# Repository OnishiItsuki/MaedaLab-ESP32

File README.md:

# Library for ESP32

2022/02/15 \
Itsuki Onishi \
E-mail : onishi.itsuki@ist.osaka-u.ac.jp

このレポジトリはESP32，ArduinoIDE環境で書かれたプログラム群です．

ESP32をArduino IDEで使うためにボード情報をインストールします． \
詳細は下記のサイトを参照してください．
 * https://github.com/espressif/arduino-esp32
 * https://dandydot.no-ip.biz/~dot/presen/advtech/seminars/iot_workshop/install-esp32-board-manager/README.md.html .

レバー角読み取りのコードは`lever_angle_reader`，モータ制御コードは`PWM_motor_controller`にあります．
それぞれの詳細は各ディレクトリ下のREADMEを読んでください．

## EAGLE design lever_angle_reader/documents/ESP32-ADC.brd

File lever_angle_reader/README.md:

# Lever angle reader for ESP32

2022/02/15 \
大西 幾月 \
E-mail : onishi.itsuki@ist.osaka-u.ac.jp

## 機能
このプログラムは，AD converter（以降ADCと記載）によるレバー角の測定と結果の送信を行います． \
操作対象となるデバイスは下記の通りです．
括弧内に使用したデバイスの型番を記載します．
  * ADC (LTC2309)
  * OLED display (SSD1306)
  * Signal LED

プログラムの流れは下記のとおりです．
  1. ESP32，ADC，OLED display，LEDの初期化．
  2. ADCに読み取りのための信号をI2Cを用いて送信．
  3. ADCから測定された電圧を受信．
  4. 電圧からPWM制御信号を生成．
  5. 測定結果をPWM_motor_controllerを稼働させているESP32に送信．
  6. 2から5の処理を繰り返す．

このプログラムは"PWM_motor_controller"とセットで使います．
"PWM_motor_controller"の詳細は同名のディレクトリ下にあるREADMEを参照してください．

## 依存環境
ESP32をArduino IDEで使うためにボード情報をインストールします． \
詳細は下記のサイトを参照してください．
 * https://github.com/espressif/arduino-esp32
 * https://dandydot.no-ip.biz/~dot/presen/advtech/seminars/iot_workshop/install-esp32-board-manager/README.md.html .

依存するライブラリを列挙します．
それぞれのライブラリの詳細はライブラリ名の下に記載したサイトを参照してください．

  * ESP8266 and ESP32 driver for SSD1366 displays
    * https://wak-tech.com/archives/825
    * https://github.com/ThingPulse/esp8266-oled-ssd1306

## ファイル構成
このプログラムのファイル構成は下記の通りです．
```  
.  
|-- documents
|   |-- ESP32-ADC.brd           # このデバイスの基盤設計図（ボード情報）
|   |-- ESP32-ADC.sch           # このデバイスの基盤設計図（配線情報）
|   --- LTC2309.pdf             # ADC (LTC2309)のデータシート
|
|-- lever_angle_reader.ino      # Main
|-- ADC_controller.ino          # ADC用の関数と変数
|-- OLED_controller.ino         # OLED用の関数と変数
|-- SIGNAL_LED_controller.ino   # Signal LED用の関数
|-- UDP_Tx.ino                  # WiFi+UDPによる信号送信用の関数
--- README.md                   # このファイル
```

## 通信フォーマット
"PWM_motor_controller"下のREADME内の同項目を参照してください．

## 関数リスト
各ファイルにある関数の情報です．
各ファイル内でのみアクセスする関数は"_"を先頭に付けています．

### lever_angle_reader.ino
| 関数名 | 構文 | 機能 | 返り値 | 処理説明 | 備考 |
| :---: | :---: | :---: | :---: | :---: | :---: |
| setup | setup() | デバイス全体の初期化 | Nan | ESP32，AD converter，OLED，LEDの初期化とチェック処理 |  |
| loop | loop() | ESP32のmain loop | Nan | レバー角の読み取りと送信 |  |

### ADC_controller.ino
| 関数名 | 構文 | 機能 | 返り値 | 処理説明 | 備考 |
| :---: | :---: | :---: | :---: | :---: | :---: |
| ADC_init | ADC_init() | ADCの利用時に`setup()`で呼ぶ関数 | Nan | ADCのデバイスの初期化（？）とESP32側でのADC利用のための処理 | 未実装 |
| _send_read_signal | _send_read_signal() | ADCに読み取り信号を送る． | Nan | ADC用にI2C回線を専有し，読み取り信号を送信する．step2の処理に相当する． | 未実装 |
| _receive_voltage_values | _receive_voltage_values(int buffer[]) | ADCから観測値を取得する． | Nan | ADCから観測値を取得し，受け取った配列に格納する．step3の処理に相当する．| 未実装 |
| read_voltage_from_ADC | read_voltage_from_ADC(int buffer[]) | ADCから観測値を取得する． | Nan | `lever_angle_reader.ino`からADCにアクセスするための関数．内部では_send_read_signalと_receive_voltage_valuesを呼び出している． |  |

### OLED_controller.ino
| 関数名 | 構文 | 機能 | 返り値 | 処理説明 | 備考 |
| :---: | :---: | :---: | :---: | :---: | :---: |
| OLED_init | OLED_init() | OLEDディスプレイの利用時に`setup()`で呼ぶ関数 | Nan | ディスプレイの初期化と異常検知用の全要素表示を行う． |  |
| disp_init | disp_init() | ディスプレイの初期化 | Nan | 初期化とフォント（フォントサイズを含む）設定を行う． |  |
| OLED_clear | OLED_clear() | ディスプレイの表示を消す | Nan | ディスプレイの表示を消す． | 今はdisp_init()を呼び出すことで実装している．もう少しいい方法があるかも． |
| disp_all_pixel | disp_all_pixel() | 全画素をONにする | Nan | 全画素をONにする |  |
| disp_add_string | disp_add_string(int16_t x, int16_t y, String message) | ディスプレイに文字を表示する． | Nan | messageに入力された文字列を(x, y)の位置に出力する．過去のディスプレイの表示は消されずに追加される． |  |
| disp_show_string | disp_show_string(String message) | 入力された文字列を成型して表示 | Nan | messageで入力された文字列を画面端もしくは"\n"で折り返す．縦方向には特に処理を行わないのであまり多くの文字を各と画面下で文字が切れる．（簡単な判定で警告を出す機能はある．） | 2行まではうまく表示できるはず．．．あまり期待した動作をしなさそうです．．． |

### SIGNAL_LED_controller.ino
| 関数名 | 構文 | 機能 | 返り値 | 処理説明 | 備考 |
| :---: | :---: | :---: | :---: | :---: | :---: |
| LED_init | LED_init() | LEDを使うときに最初に呼び出す関数 | Nan | ピンアサインを行う．PIN番号はSIGNAL_LED_PINにより設定する． |  |
| led_on | led_on() | LEDを点灯する． | Nan | LEDを点灯する． |  |
| led_off | led_off() | LEDを消灯する． | Nan | LEDを消灯する． |  |

### UDP_Tx.ino
| 関数名 | 構文 | 機能 | 返り値 | 処理説明 | 備考 |
| :---: | :---: | :---: | :---: | :---: | :---: |
| _WiFi_setup | _WiFi_setup(String message) | ESP32間の通信を担うWiFiの初期化 | Nan | WiFiインスタンスの初期化と設定を行う．Serial通信とディスプレイでの状態表示をも行う．messageには何のために呼び出されたかの説明を入れる． | WiFiが接続されるまでloopし続けるので注意．（特に単体でdebugするとき） |
| _signal_buffer_init | _signal_buffer_init() | signal_bufferの初期化 | Nan | signal_bufferを初期化する． |  |
| UDP_init | UDP_init() | ESP32間の通信を行う際に`setup()`で呼ぶ関数 | Nan | UDPを用いたWiFiの初期化処理と接続を行う．接続に成功したらその旨をSerial通信とディスプレイで表示する． |  |
| _compute_signal_from_voltage | _compute_signal_from_voltage(int voltage_value) | WiFiで送信される値を計算する |WiFiで送信される値 | ADCで観測した電圧からWiFiで送信する値を計算する．入力，出力ともに配列ではなく，値であることに注意． | 現状intからuint8_tにコンバートするだけの関数になっている． |
| _compute_parity | _compute_parity(uint8_t signal_buffer[]) | parity bitの値を計算する | parity bitの値 | index 1からindex NUM_CH-2までにWiFiで送信される値を格納した配列を受け取り，parity bitの値を計算して返す． |  |
| _generate_udp_signal_from_voltage | _generate_udp_signal_from_voltage(int voltage[]) | WiFiで送信する値の生成 | Nan | ADCで観測した値の配列からWiFiで送信する信号を生成する．結果はsignal_bufferに格納される． |  |
| _send_signal | _send_signal() | WiFiでsignal_bufferの値を送信する | Nan | WiFiの接続を確認し，signal_bufferの値を送信する．WiFiの接続が切れていた場合は再接続処理を行う．急激な動きを防ぐために，関数の実行後に送信の可否に寄らずsignal_bufferの値は初期化される． | WiFiが接続されない間はloopし続けるので注意 |
| send_udp_signal | send_udp_signal(int voltage[]) | ADCの観測結果をWiFiで送信する | Nan | ADCでの観測結果を受け取り，前処理の後にWiFiで相手のESP32に送信する． |  |

## 変数リスト
各ファイルにある変数の情報です．
local変数については説明を省略します．
マクロは大文字スネーク記法，変数は小文字スネーク記法（省略した単語は大文字）で書いています．
設定値は基本的にマクロで書いています．

### lever_angle_reader.ino
| 変数名 | 用途 | 備考 |
| :---: | :---: | :---: |
| SDA_PIN | I2C通信のSDAのPINを決める．使えるPINに制約があるので，ググって調べてください． | デフォルトは21（`ADC_controller.ino`と`OLED_controller.ino`で定義） |
| SCL_PIN | I2C通信のSCLのPINを決める．使えるPINに制約があるので，ググって調べてください． | デフォルトは22（`ADC_controller.ino`と`OLED_controller.ino`で定義） |
| SIGNAL_LED_PIN | LEDの制御PINを決める． | デフォルトは27（`SIGNAL_LED_controller.ino`で定義） |
| NUM_CH | ADCで読み取る信号のチャネル数．6で固定でOK（マジックナンバー回避が目的のため） |  |
| voltage_buffer | ADCで読み取った数値を格納する配列． | 現在はint型にしていますが，ADCの仕様に合わせて変えてください． |

### ADC_controller.ino
| 変数名 | 用途 | 備考 |
| :---: | :---: | :---: |
| SDA_PIN | I2C通信のSDAのPINを決める．使えるPINに制約があるので，ググって調べてください． | この値は基本的に変更しない．一時的に変更する場合は，`lever_angle_reader.ino`に書く． |
| SCL_PIN | I2C通信のSCLのPINを決める．使えるPINに制約があるので，ググって調べてください． | この値は基本的に変更しない．一時的に変更する場合は，`lever_angle_reader.ino`に書く． |
| MAX_SLAVE_RESPONSE_LENGTH | ADCに要求するバイト数． | ADC実装後に確認 |
| ADC_ADDR | ADCのI2C通信におけるアドレス． |  |

### OLED_controller.ino
| 変数名 | 用途 | 備考 |
| :---: | :---: | :---: |
| SDA_PIN | I2C通信のSDAのPINを決める．使えるPINに制約があるので，ググって調べてください． | この値は基本的に変更しない．一時的に変更する場合は，`lever_angle_reader.ino`に書く． |
| SCL_PIN | I2C通信のSCLのPINを決める．使えるPINに制約があるので，ググって調べてください． | この値は基本的に変更しない．一時的に変更する場合は，`lever_angle_reader.ino`に書く． |
| OLED_ADDR | OLEDディスプレイのI2C通信でのアドレス． |  |
| FONT | ディスプレイのフォントとフォントサイズを決める．入力値の詳細はググってください． |  |
| font_size_width | フォントの横幅に相当する定数．これでフォントサイズが変わるわけでは無く，`disp_show_string`の成型に影響する．表示を見ながら適当に設定指定ください． |  |
| font_size_height | フォントの縦幅に相当する定数．これでフォントサイズが変わるわけでは無く，`disp_show_string`の成型に影響する．表示を見ながら適当に設定指定ください． |  |
| disp_width | ディスプレイの横幅．`disp_all_pixel`などで使用している． | 調整済みなので，128から変更しない．
| disp_height | ディスプレイの縦幅．`disp_all_pixel`などで使用している． | 調整済みなので，64から変更しない． |
| max_num_char_width | 横幅に入る最大文字数．上記の変数から計算するので設定不要． |  |
| max_num_line | ディスプレイに表示できる最大行数．上記の変数から計算するので設定不要． |  |

### SIGNAL_LED_controller.ino
| 変数名 | 用途 | 備考 |
| :---: | :---: | :---: |
| SIGNAL_LED_PIN | LEDの制御PINを決める． | この値は基本的に変更しない．一時的に変更する場合は，`lever_angle_reader.ino`に書く． |

### UDP_Tx.ino
| 変数名 | 用途 | 備考 |
| :---: | :---: | :---: |
| SSID | WiFiホストのSSID．なんでもいいが，ホストと一致させる必要がある． |  |
| PASSWORD | WiFiホストのPASSWORD．なんでもいいが，ホストと一致指せる必要がある． |  |
| HOST_IP | WiFiホストのIP．なんでもいいが，ホストと一致指せる必要がある． |  |
| HOST_PORT | ホストのソケットのポート設定．なんでもいいが，ホストと一致指せる必要がある． |  |
| CLIENT_PORT | クライアントのソケットのポート設定．なんでもいい． |  |
| RECONNECTION_SPAN_MS | WiFiの接続が切れている時に接続を再確認する時間間隔． |  |
| signal_size | UDPで送信する信号のサイズ．スタートビット，各チャネルの信号，パリティビットで構成されるため，NUM_CH + 2となっている． |  |
| start_BYTE | スタートバイトの値． |  |
| signal_buffer | 送信する信号のbuffer． |  |

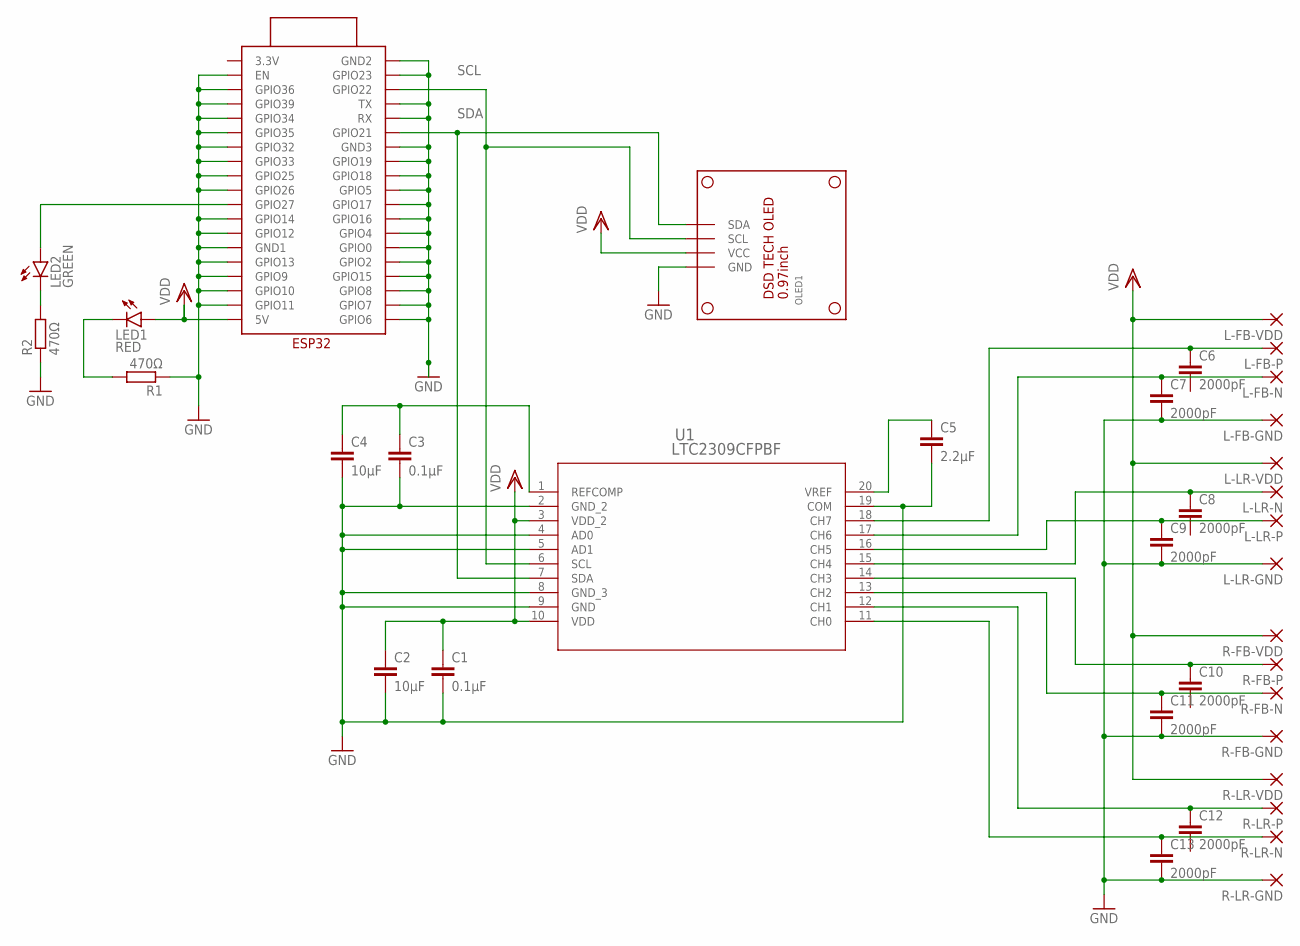
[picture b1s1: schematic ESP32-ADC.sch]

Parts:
C1, C3: 0.1µF; C3216
C2, C4: 10µF; C3216
C5: 2.2µF; C3216
C6, C7, C8, C9, C10, C11, C12, C13: 2000pF; C3216
L-FB-GND: SMD2; SMD1,27-2,54
L-FB-N: SMD2; SMD1,27-2,54
L-FB-P: SMD2; SMD1,27-2,54
L-FB-VDD: SMD2; SMD1,27-2,54
L-LR-GND: SMD2; SMD1,27-2,54
L-LR-N: SMD2; SMD1,27-2,54
L-LR-P: SMD2; SMD1,27-2,54
L-LR-VDD: SMD2; SMD1,27-2,54
LED1: RED; LED3MM
LED2: GREEN; LED3MM
OLED1: DSDTECH_ARDUINO_AVRCOMPATIBLE_IIC_OLED; DSDTECH0.96"ARDUINOAVRCOMPATIBLEIICOLEDLCDSCREENSUPPORTU8GL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
R1, R2: 470Ω; R3216W
R-FB-GND: SMD2; SMD1,27-2,54
R-FB-N: SMD2; SMD1,27-2,54
R-FB-P: SMD2; SMD1,27-2,54
R-FB-VDD: SMD2; SMD1,27-2,54
R-LR-GND: SMD2; SMD1,27-2,54
R-LR-N: SMD2; SMD1,27-2,54
R-LR-P: SMD2; SMD1,27-2,54
R-LR-VDD: SMD2; SMD1,27-2,54
U1: LTC2309CFPBF; TSSOP-20_F_LIT
U$2: ESP32ESP32_WIFI; ESP32_WIFI

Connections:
GND: C1.2, C2.2, C3.2, C4.2, C5.2, C7.2, C9.2, C11.2, C13.2, L-FB-GND.1, L-LR-GND.1, OLED1.GND, R1.1, R2.1, R-FB-GND.1, R-LR-GND.1, U1.2 (GND_2), U1.4 (AD0), U1.5 (AD1), U1.8 (GND_3), U1.9 (GND), U1.19 (COM), U$2.EN, U$2.GND1, U$2.GND2, U$2.GND3, U$2.GPIO0, U$2.GPIO2, U$2.GPIO4, U$2.GPIO5, U$2.GPIO6, U$2.GPIO7, U$2.GPIO8, U$2.GPIO9, U$2.GPIO10, U$2.GPIO11, U$2.GPIO12, U$2.GPIO13, U$2.GPIO14, U$2.GPIO15, U$2.GPIO16, U$2.GPIO17, U$2.GPIO18, U$2.GPIO19, U$2.GPIO23, U$2.GPIO25, U$2.GPIO26, U$2.GPIO32, U$2.GPIO33, U$2.GPIO34, U$2.GPIO35, U$2.GPIO36, U$2.GPIO39, U$2.RX, U$2.TX
unnamed: C5.1, U1.20 (VREF)
unnamed: LED2.A, U$2.GPIO27
unnamed: C6.1, L-FB-P.1, U1.18 (CH7)
unnamed: C7.1, L-FB-N.1, U1.17 (CH6)
unnamed: C9.1, L-LR-P.1, U1.16 (CH5)
unnamed: C8.1, L-LR-N.1, U1.15 (CH4)
unnamed: C10.1, R-FB-P.1, U1.14 (CH3)
unnamed: C11.1, R-FB-N.1, U1.13 (CH2)
unnamed: C13.1, R-LR-N.1, U1.11 (CH0)
unnamed: C12.1, R-LR-P.1, U1.12 (CH1)
unnamed: LED1.K (C), R1.2
unnamed: LED2.K (C), R2.2
SCL: OLED1.SCL, U1.6 (SCL), U$2.GPIO22
SDA: OLED1.SDA, U1.7 (SDA), U$2.GPIO21
VCC1: C3.1, C4.1, U1.1 (REFCOMP)
VDD: C1.1, C2.1, L-FB-VDD.1, L-LR-VDD.1, LED1.A, OLED1.VCC, R-FB-VDD.1, R-LR-VDD.1, U1.3 (VDD_2), U1.10 (VDD), U$2.5V

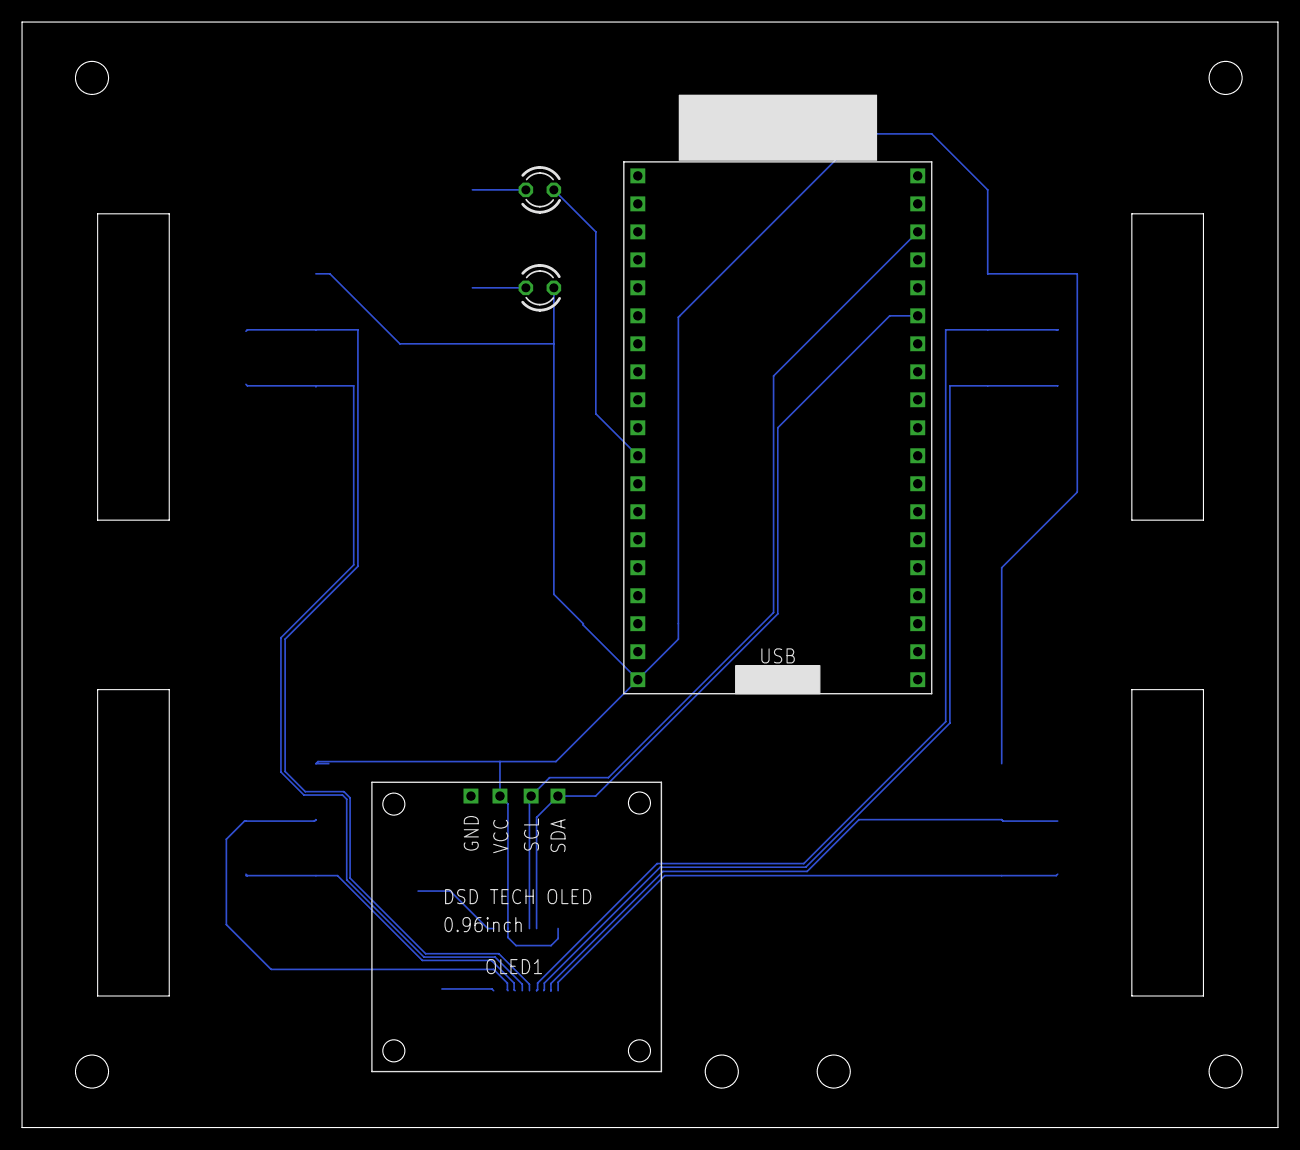
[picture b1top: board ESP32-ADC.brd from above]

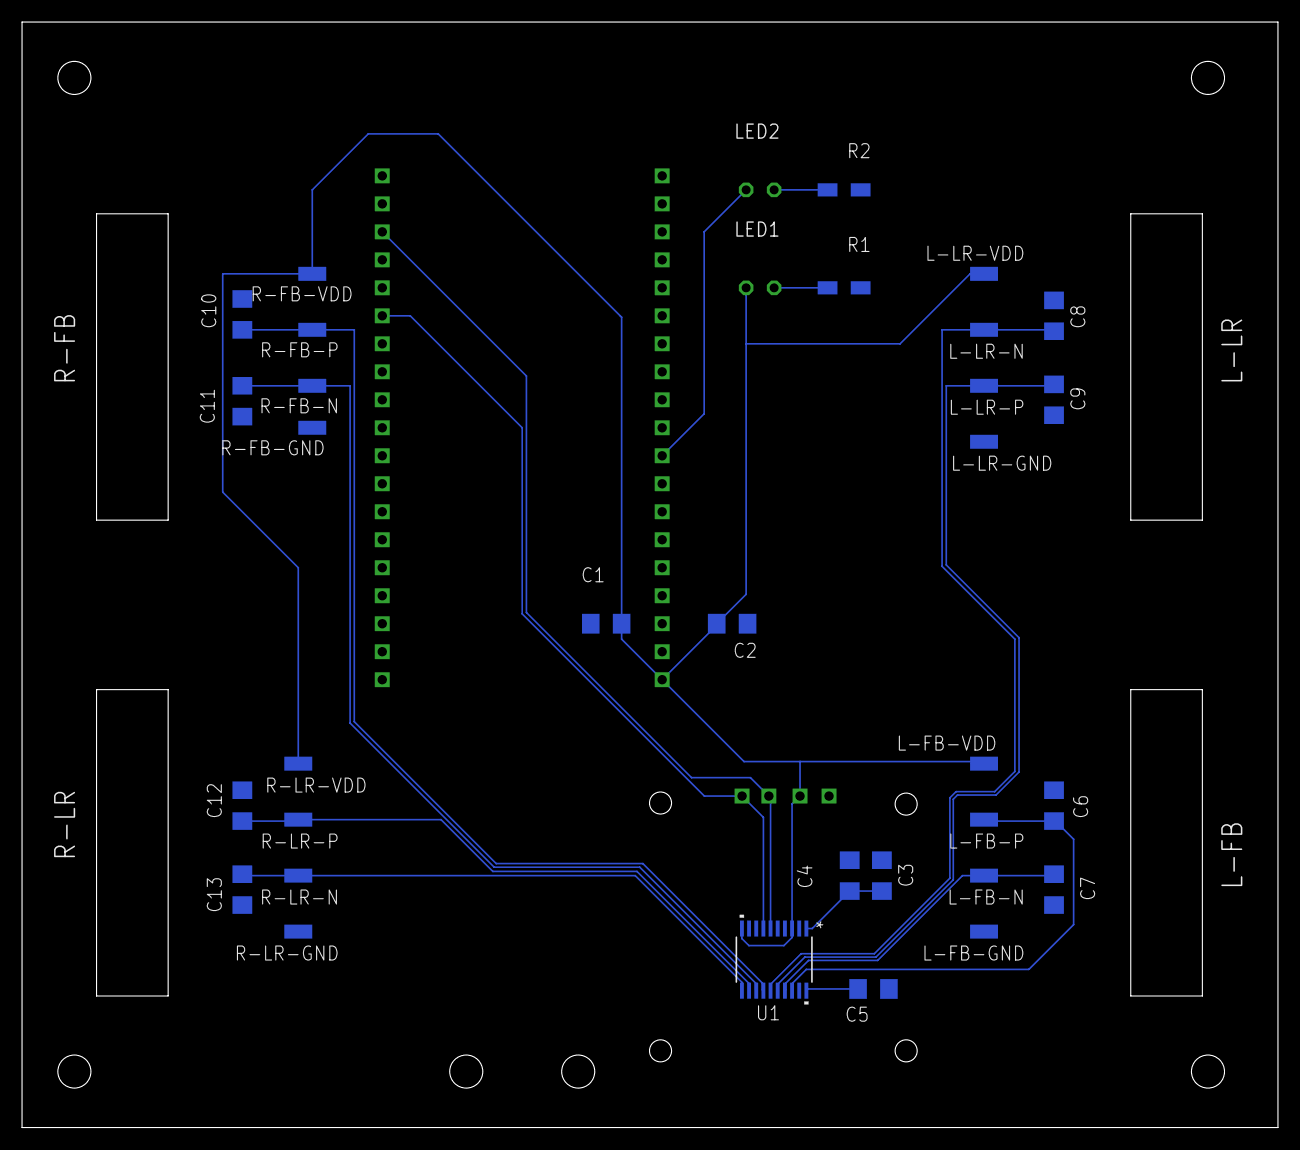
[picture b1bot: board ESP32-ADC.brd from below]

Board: 2 copper layers, 114.0 x 100.3 mm, 36 parts (32 on the bottom side), 17 nets.

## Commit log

2020-10-23 my first commit
2020-10-30 change PWM controler to run on EPS32-WROVER-B. But, I can't include Ticker_EPS32 package.
2020-11-05 share
2020-11-06 change how to set output pin (intager to define) and library name (Ticker.h to ESP32_Tickre.h)
2020-11-06 add test sckech
2020-11-13 Making PWM controler is over. this commit include test part
2020-11-13 PWM-controler.ino in this commit remove test code, but handling of input signal is not include. TODO is show by comment
2020-11-13 bugfix of PWM-controler, and make WiFi_test_Tx.ino and WiFi_test_Rx.ino. WebServer code is written in ~Tx.ino
2020-11-20 first commit of UDP. This code can not access from iPhone and ESP32
2020-11-27 UDP connection is not working
2020-11-27 if WiFi is not connected, print Disconnected
2020-12-18 UDP access was succssed
2020-12-18 change loop function to Furukawa-sennsei's loop function
2020-12-18 revert Wifi_test_Tx
2020-12-18 finish making Tx with UDP part in Wifi_test_Tx.ino
2020-12-18 finishi making Rx prat with UDP in Wifi_test_Rx.ino
2020-12-18 try to make PWM_controler as the other file in Wifi_test_Rx sketh, but it has error
2020-12-25 debug PWM-controler
2020-12-25 [Rx]finish making code processing from UDP to PWM
2020-12-25 [Tx] finish making code processing from UDP to PWM
2020-12-25 change name of some files (WiFi_Rx -> UDP_AP_Rx, WiFi_Tx -> UDP_Tx
2021-01-15 make AD_converter.ino
2021-01-15 debug AD_converter
2021-01-15 support two analog input in AD_converter
2021-02-12 make AD_converter.ino in UDP_Tx
2021-02-12 make caribration code
2021-02-12 making AD_converter func, but it output only 0.
2021-02-19 make I2C communication test
2021-02-26 make i2c_slave.ino
2021-02-26 make i2c_slabe with WireSlave library
2021-02-26 make i2c_master with WireSlave library but this is not work
2021-02-26 modify i2c_slave for example
2021-03-05 add slave code
2021-03-05 add DigitalInputPullup and I2C_slave_test
2021-03-12 modify i2c_master
2021-03-12 modify i2c_slave to use with seeeduino xiao
2021-11-01 add lever_angle_reader
2021-11-29 making SPI protocol test
2021-12-13 make SPI_xx_test files
2021-12-13 modify SPI_slave_test.ino
2021-12-13 modify SPI_master_test.ino
2021-12-20 add .vscode
2021-12-20 test SPI with simpler core
2021-12-20 modify SPI_slave_test
2021-12-20 modify SPI_master_test
2022-02-15 making documents
2022-02-15 writting readme
2022-02-21 make pipeline of code
2022-02-21 make usefull display function
2022-02-21 change the structure of functions
2022-02-21 write README
2022-02-22 refactoring and writing README
2022-02-22 refuctoring and writing README
2022-02-22 slightly change
2022-02-22 debug
2022-02-22 debug disp_show_string

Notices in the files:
parts and their libraries:
COPYRIGHT: Copyright (C) 2021 Ultra Librarian. All rights reserved.
